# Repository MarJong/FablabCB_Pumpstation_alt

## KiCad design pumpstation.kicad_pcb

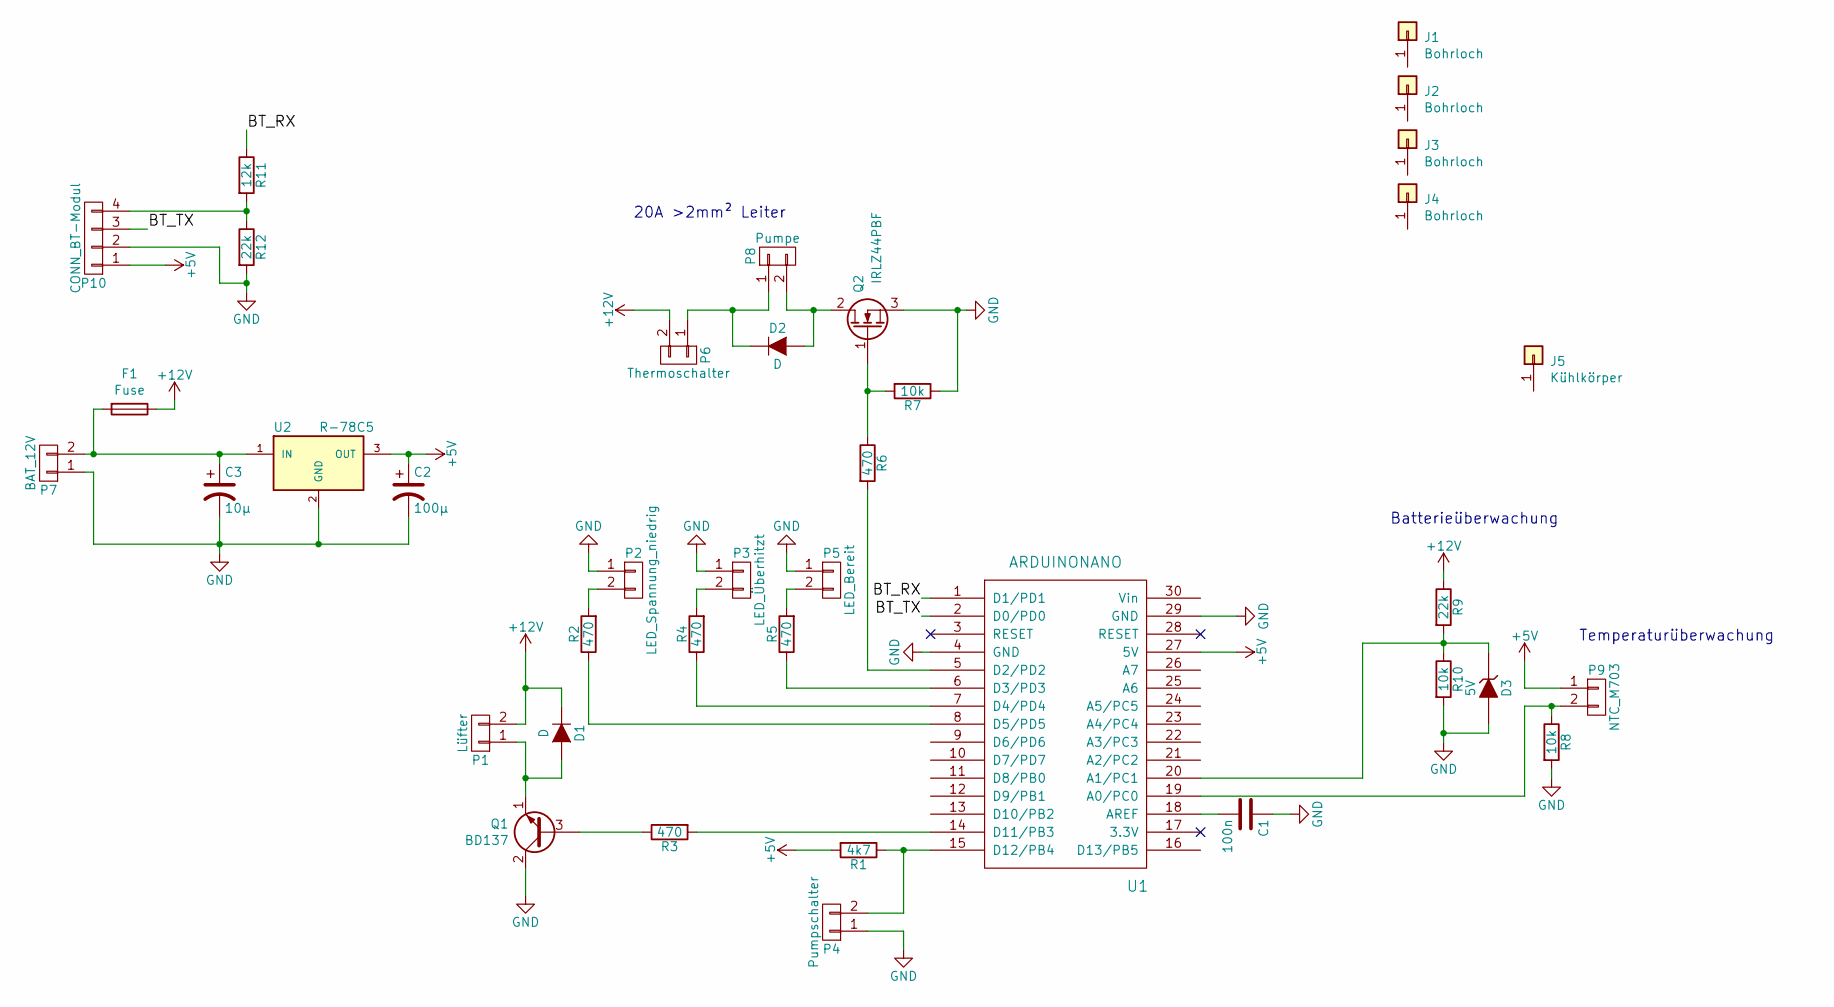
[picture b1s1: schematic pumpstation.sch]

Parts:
C1: 100n; C_Disc_D5.0mm_W2.5mm_P2.50mm
C2: 100µ; CP_Radial_D5.0mm_P2.50mm
C3: 10µ; CP_Radial_D5.0mm_P2.50mm
D1: D; D_A-405_P12.70mm_Horizontal
D2: D; D_5KPW_P12.70mm_Horizontal
D3: 5V; D_A-405_P10.16mm_Horizontal
F1: Fuse; Fuse 10x38
J1, J2, J3, J4: Bohrloch; Pin_D1.0mm_L10.0mm_LooseFit
J5: Kühlkörper; ASSMANN Kühlkörper
P1: Lüfter; PhoenixContact MKDS
P2: LED_Spannung_niedrig; PhoenixContact MKDS
P3: LED_Überhitzt; PhoenixContact MKDS
P4: Pumpschalter; PhoenixContact MKDS
P5: LED_Bereit; PhoenixContact MKDS
P6: Thermoschalter; PhoenixContact MKDS
P7: BAT_12V; PhoenixContact MKDS
P8: Pumpe; PhoenixContact MKDS
P9: NTC_M703; PinHeader_1x02_P2.54mm_Vertical
P10: CONN_BT-Modul; PinSocket_1x04_P2.54mm_Vertical
Q1: BD137; TO-126-3_Vertical
Q2: IRLZ44PBF; TO-220-3_Vertical
R1: 4k7; R_Axial_DIN0207_L6.3mm_D2.5mm_P10.16mm_Horizontal
R2, R3, R4, R5, R6: 470; R_Axial_DIN0207_L6.3mm_D2.5mm_P10.16mm_Horizontal
R7, R8, R10: 10k; R_Axial_DIN0207_L6.3mm_D2.5mm_P10.16mm_Horizontal
R9, R12: 22k; R_Axial_DIN0207_L6.3mm_D2.5mm_P10.16mm_Horizontal
R11: 12k; R_Axial_DIN0207_L6.3mm_D2.5mm_P10.16mm_Horizontal
U1: ARDUINONANO; Arduino Nano
U2: R-78C5; RECOM R-7850

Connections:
+5V: C2.1, P9.1, P10.1, R1.2, U1.27 (5V), U2.3 (OUT)
+12V: D1.1 (K), F1.1, P1.2, P6.2, R9.1
/BT_RX: R11.1, U1.1 (D1/PD1)
/BT_TX: P10.3, U1.2 (D0/PD0)
GND: C1.1, C2.2, C3.2, D3.2 (A), P2.1, P3.1, P4.1, P5.1, P7.1, P10.2, Q1.2 (C), Q2.3 (S), R7.1, R8.2, R10.2, R12.2, U1.4 (GND), U1.29 (GND), U2.2 (GND)
unnamed: C1.2, U1.18 (AREF)
unnamed: C3.1, F1.2, P7.2, U2.1 (IN)
unnamed: D1.2 (A), P1.1, Q1.1 (E)
unnamed: D2.1 (K), P6.1, P8.1
unnamed: D2.2 (A), P8.2, Q2.2 (D)
unnamed: D3.1 (K), R9.2, R10.1, U1.20 (A1/PC1)
unnamed: P2.2, R2.2
unnamed: P3.2, R4.2
unnamed: P4.2, R1.1, U1.15 (D12/PB4)
unnamed: P5.2, R5.2
unnamed: P9.2, R8.1, U1.19 (A0/PC0)
unnamed: P10.4, R11.2, R12.1
unnamed: Q1.3 (B), R3.1
unnamed: Q2.1 (G), R6.1, R7.2
unnamed: R2.1, U1.8 (D5/PD5)
unnamed: R3.2, U1.14 (D11/PB3)
unnamed: R4.1, U1.7 (D4/PD4)
unnamed: R5.1, U1.6 (D3/PD3)
unnamed: R6.2, U1.5 (D2/PD2)

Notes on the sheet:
20A >2mm² Leiter
Temperaturüberwachung
Batterieüberwachung

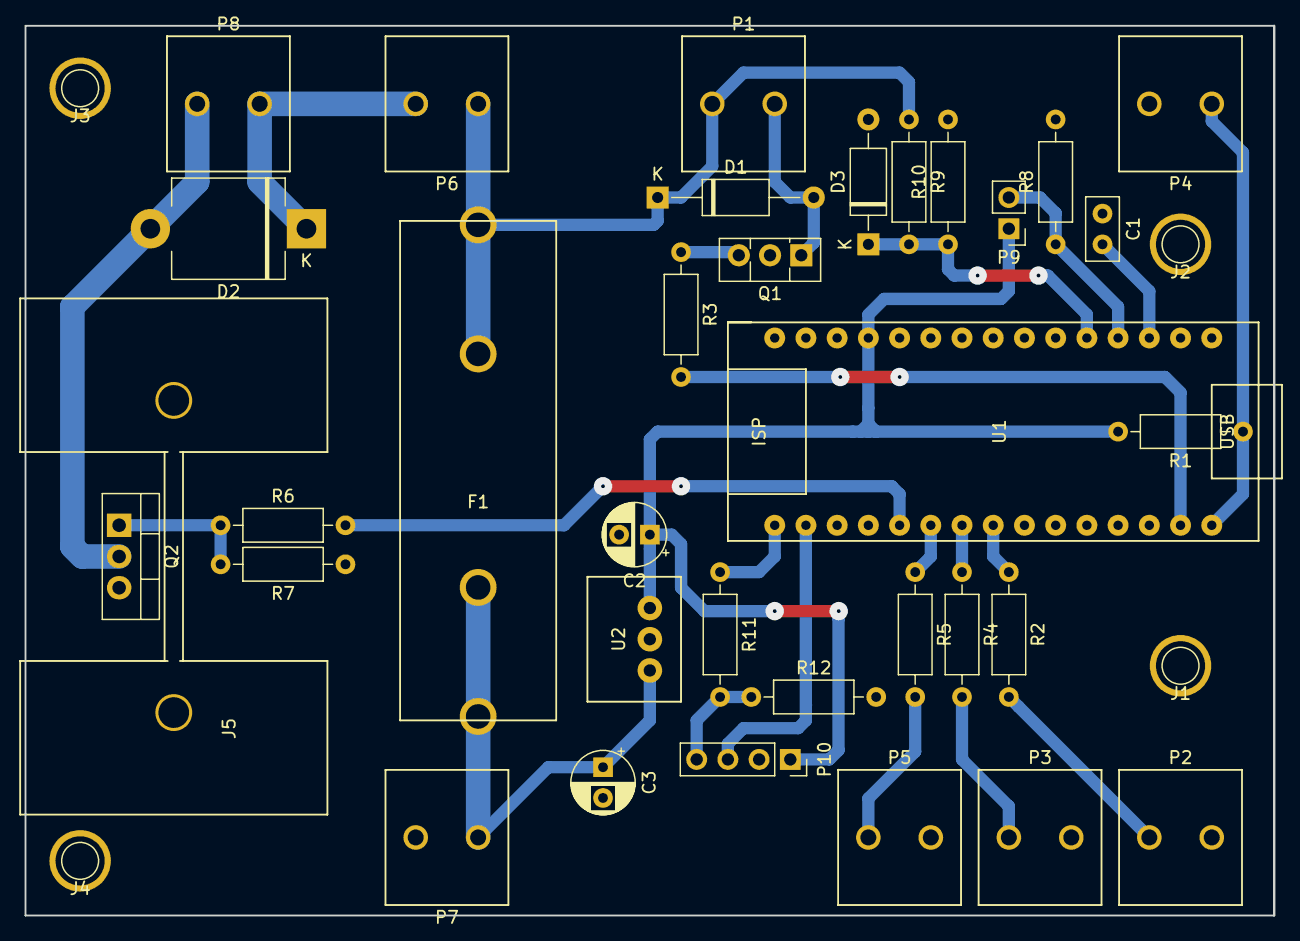
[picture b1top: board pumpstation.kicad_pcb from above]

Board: 2 copper layers, 101.6 x 72.4 mm, 38 parts (0 on the bottom side), 24 nets.
